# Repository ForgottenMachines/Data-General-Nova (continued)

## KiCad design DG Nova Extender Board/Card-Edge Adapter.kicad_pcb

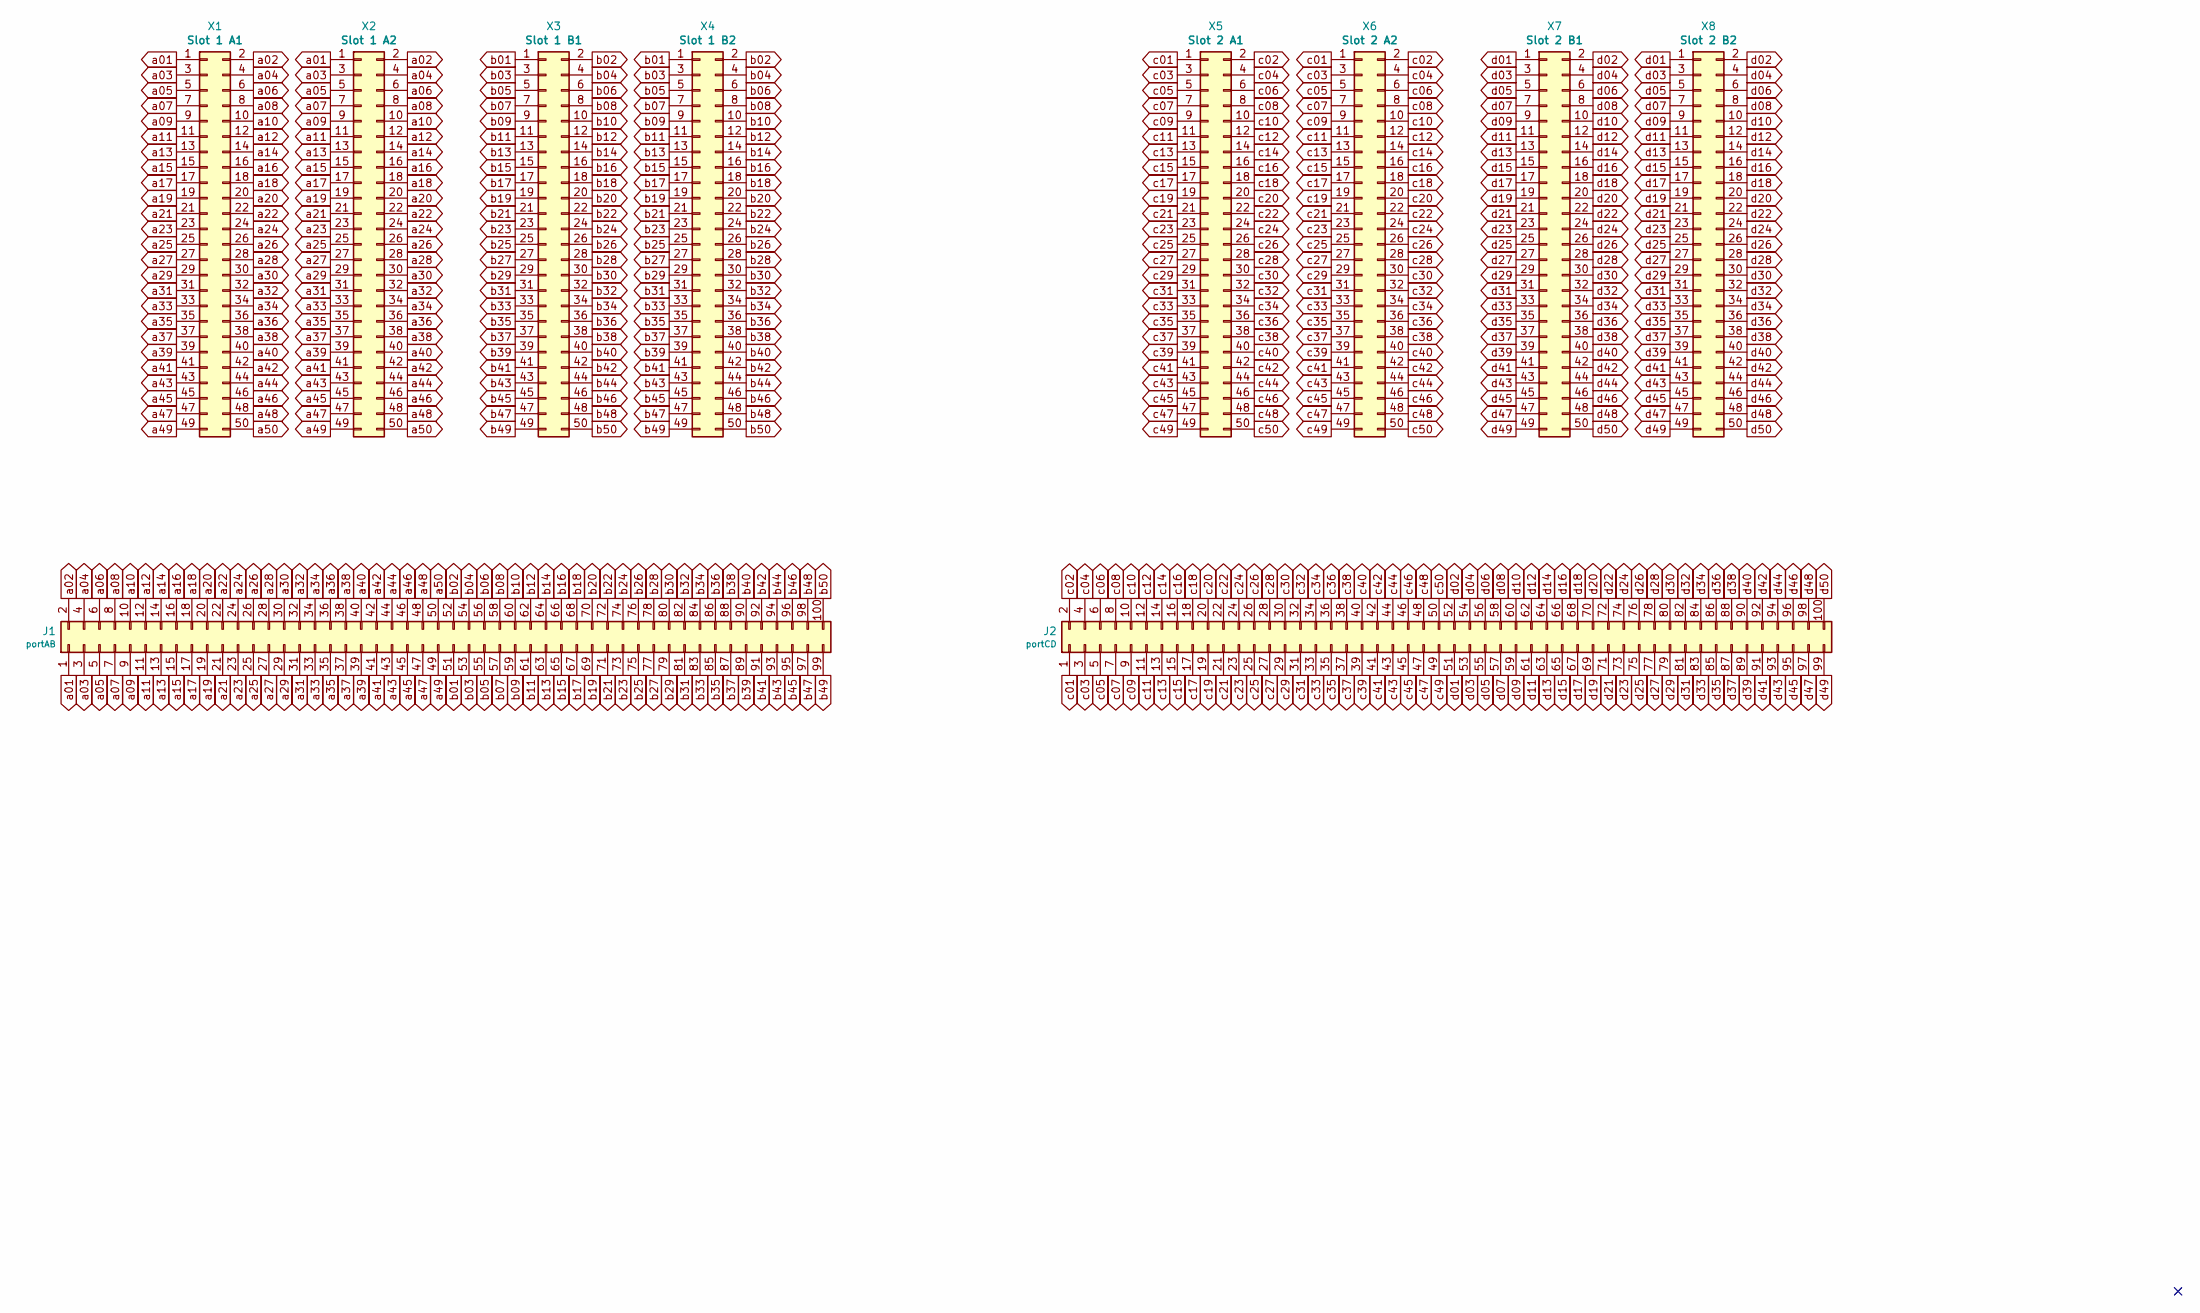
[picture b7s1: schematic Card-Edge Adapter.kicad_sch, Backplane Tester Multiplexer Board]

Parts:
J1: portAB; portA_NovaMod
J2: portCD; portB_NovaMod
X1: Slot 1 A1; IDC-Header_2x25_P2.54mm_Vertical; Part-Number SBH11-PBPC-D25-ST-BK; Digi-Key S9176-ND
X2: Slot 1 A2; IDC-Header_2x25_P2.54mm_Vertical; Part-Number SBH11-PBPC-D25-ST-BK; Digi-Key S9176-ND
X3: Slot 1 B1; IDC-Header_2x25_P2.54mm_Vertical; Part-Number SBH11-PBPC-D25-ST-BK; Digi-Key S9176-ND
X4: Slot 1 B2; IDC-Header_2x25_P2.54mm_Vertical; Part-Number SBH11-PBPC-D25-ST-BK; Digi-Key S9176-ND
X5: Slot 2 A1; IDC-Header_2x25_P2.54mm_Vertical; Part-Number SBH11-PBPC-D25-ST-BK; Digi-Key S9176-ND
X6: Slot 2 A2; IDC-Header_2x25_P2.54mm_Vertical; Part-Number SBH11-PBPC-D25-ST-BK; Digi-Key S9176-ND
X7: Slot 2 B1; IDC-Header_2x25_P2.54mm_Vertical; Part-Number SBH11-PBPC-D25-ST-BK; Digi-Key S9176-ND
X8: Slot 2 B2; IDC-Header_2x25_P2.54mm_Vertical; Part-Number SBH11-PBPC-D25-ST-BK; Digi-Key S9176-ND

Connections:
a01: J1.1, X1.1, X2.1
a02: J1.2, X1.2, X2.2
a03: J1.3, X1.3, X2.3
a04: J1.4, X1.4, X2.4
a05: J1.5, X1.5, X2.5
a06: J1.6, X1.6, X2.6
a07: J1.7, X1.7, X2.7
a08: J1.8, X1.8, X2.8
a09: J1.9, X1.9, X2.9
a10: J1.10, X1.10, X2.10
a11: J1.11, X1.11, X2.11
a12: J1.12, X1.12, X2.12
a13: J1.13, X1.13, X2.13
a14: J1.14, X1.14, X2.14
a15: J1.15, X1.15, X2.15
a16: J1.16, X1.16, X2.16
a17: J1.17, X1.17, X2.17
a18: J1.18, X1.18, X2.18
a19: J1.19, X1.19, X2.19
a20: J1.20, X1.20, X2.20
a21: J1.21, X1.21, X2.21
a22: J1.22, X1.22, X2.22
a23: J1.23, X1.23, X2.23
a24: J1.24, X1.24, X2.24
a25: J1.25, X1.25, X2.25
a26: J1.26, X1.26, X2.26
a27: J1.27, X1.27, X2.27
a28: J1.28, X1.28, X2.28
a29: J1.29, X1.29, X2.29
a30: J1.30, X1.30, X2.30
a31: J1.31, X1.31, X2.31
a32: J1.32, X1.32, X2.32
a33: J1.33, X1.33, X2.33
a34: J1.34, X1.34, X2.34
a35: J1.35, X1.35, X2.35
a36: J1.36, X1.36, X2.36
a37: J1.37, X1.37, X2.37
a38: J1.38, X1.38, X2.38
a39: J1.39, X1.39, X2.39
a40: J1.40, X1.40, X2.40
a41: J1.41, X1.41, X2.41
a42: J1.42, X1.42, X2.42
a43: J1.43, X1.43, X2.43
a44: J1.44, X1.44, X2.44
a45: J1.45, X1.45, X2.45
a46: J1.46, X1.46, X2.46
a47: J1.47, X1.47, X2.47
a48: J1.48, X1.48, X2.48
a49: J1.49, X1.49, X2.49
a50: J1.50, X1.50, X2.50
b01: J1.51, X3.1, X4.1
b02: J1.52, X3.2, X4.2
b03: J1.53, X3.3, X4.3
b04: J1.54, X3.4, X4.4
b05: J1.55, X3.5, X4.5
b06: J1.56, X3.6, X4.6
b07: J1.57, X3.7, X4.7
b08: J1.58, X3.8, X4.8
b09: J1.59, X3.9, X4.9
b10: J1.60, X3.10, X4.10
b11: J1.61, X3.11, X4.11
b12: J1.62, X3.12, X4.12
b13: J1.63, X3.13, X4.13
b14: J1.64, X3.14, X4.14
b15: J1.65, X3.15, X4.15
b16: J1.66, X3.16, X4.16
b17: J1.67, X3.17, X4.17
b18: J1.68, X3.18, X4.18
b19: J1.69, X3.19, X4.19
b20: J1.70, X3.20, X4.20
b21: J1.71, X3.21, X4.21
b22: J1.72, X3.22, X4.22
b23: J1.73, X3.23, X4.23
b24: J1.74, X3.24, X4.24
b25: J1.75, X3.25, X4.25
b26: J1.76, X3.26, X4.26
b27: J1.77, X3.27, X4.27
b28: J1.78, X3.28, X4.28
b29: J1.79, X3.29, X4.29
b30: J1.80, X3.30, X4.30
b31: J1.81, X3.31, X4.31
b32: J1.82, X3.32, X4.32
b33: J1.83, X3.33, X4.33
b34: J1.84, X3.34, X4.34
b35: J1.85, X3.35, X4.35
b36: J1.86, X3.36, X4.36
b37: J1.87, X3.37, X4.37
b38: J1.88, X3.38, X4.38
b39: J1.89, X3.39, X4.39
b40: J1.90, X3.40, X4.40
b41: J1.91, X3.41, X4.41
b42: J1.92, X3.42, X4.42
b43: J1.93, X3.43, X4.43
b44: J1.94, X3.44, X4.44
b45: J1.95, X3.45, X4.45
b46: J1.96, X3.46, X4.46
b47: J1.97 (Pin_69), X3.47, X4.47
b48: J1.98, X3.48, X4.48
b49: J1.99, X3.49, X4.49
b50: J1.100, X3.50, X4.50
c01: J2.1, X5.1, X6.1
c02: J2.2, X5.2, X6.2
c03: J2.3, X5.3, X6.3
c04: J2.4, X5.4, X6.4
c05: J2.5, X5.5, X6.5
c06: J2.6, X5.6, X6.6
c07: J2.7, X5.7, X6.7
c08: J2.8, X5.8, X6.8
c09: J2.9, X5.9, X6.9
c10: J2.10, X5.10, X6.10
c11: J2.11, X5.11, X6.11
c12: J2.12, X5.12, X6.12
c13: J2.13, X5.13, X6.13
c14: J2.14, X5.14, X6.14
c15: J2.15, X5.15, X6.15
c16: J2.16, X5.16, X6.16
c17: J2.17, X5.17, X6.17
c18: J2.18, X5.18, X6.18
c19: J2.19, X5.19, X6.19
c20: J2.20, X5.20, X6.20
c21: J2.21, X5.21, X6.21
c22: J2.22, X5.22, X6.22
c23: J2.23, X5.23, X6.23
c24: J2.24, X5.24, X6.24
c25: J2.25, X5.25, X6.25
c26: J2.26, X5.26, X6.26
c27: J2.27, X5.27, X6.27
c28: J2.28, X5.28, X6.28
c29: J2.29, X5.29, X6.29
c30: J2.30, X5.30, X6.30
c31: J2.31, X5.31, X6.31
c32: J2.32, X5.32, X6.32
c33: J2.33, X5.33, X6.33
c34: J2.34, X5.34, X6.34
c35: J2.35, X5.35, X6.35
c36: J2.36, X5.36, X6.36
c37: J2.37, X5.37, X6.37
c38: J2.38, X5.38, X6.38
c39: J2.39, X5.39, X6.39
c40: J2.40, X5.40, X6.40
c41: J2.41, X5.41, X6.41
c42: J2.42, X5.42, X6.42
c43: J2.43, X5.43, X6.43
c44: J2.44, X5.44, X6.44
c45: J2.45, X5.45, X6.45
c46: J2.46, X5.46, X6.46
c47: J2.47, X5.47, X6.47
c48: J2.48, X5.48, X6.48
c49: J2.49, X5.49, X6.49
c50: J2.50, X5.50, X6.50
d01: J2.51, X7.1, X8.1
d02: J2.52, X7.2, X8.2
d03: J2.53, X7.3, X8.3
d04: J2.54, X7.4, X8.4
d05: J2.55, X7.5, X8.5
d06: J2.56, X7.6, X8.6
d07: J2.57, X7.7, X8.7
d08: J2.58, X7.8, X8.8
d09: J2.59, X7.9, X8.9
d10: J2.60, X7.10, X8.10
d11: J2.61, X7.11, X8.11
d12: J2.62, X7.12, X8.12
d13: J2.63, X7.13, X8.13
d14: J2.64, X7.14, X8.14
d15: J2.65, X7.15, X8.15
d16: J2.66, X7.16, X8.16
d17: J2.67, X7.17, X8.17
d18: J2.68, X7.18, X8.18
d19: J2.69, X7.19, X8.19
d20: J2.70, X7.20, X8.20
d21: J2.71, X7.21, X8.21
d22: J2.72, X7.22, X8.22
d23: J2.73, X7.23, X8.23
d24: J2.74, X7.24, X8.24
d25: J2.75, X7.25, X8.25
d26: J2.76, X7.26, X8.26
d27: J2.77, X7.27, X8.27
d28: J2.78, X7.28, X8.28
d29: J2.79, X7.29, X8.29
d30: J2.80, X7.30, X8.30
d31: J2.81, X7.31, X8.31
d32: J2.82, X7.32, X8.32
d33: J2.83, X7.33, X8.33
d34: J2.84, X7.34, X8.34
d35: J2.85, X7.35, X8.35
d36: J2.86, X7.36, X8.36
d37: J2.87, X7.37, X8.37
d38: J2.88, X7.38, X8.38
d39: J2.89, X7.39, X8.39
d40: J2.90, X7.40, X8.40
d41: J2.91, X7.41, X8.41
d42: J2.92, X7.42, X8.42
d43: J2.93, X7.43, X8.43
d44: J2.94, X7.44, X8.44
d45: J2.95, X7.45, X8.45
d46: J2.96, X7.46, X8.46
d47: J2.97 (Pin_69), X7.47, X8.47
d48: J2.98, X7.48, X8.48
d49: J2.99, X7.49, X8.49
d50: J2.100, X7.50, X8.50

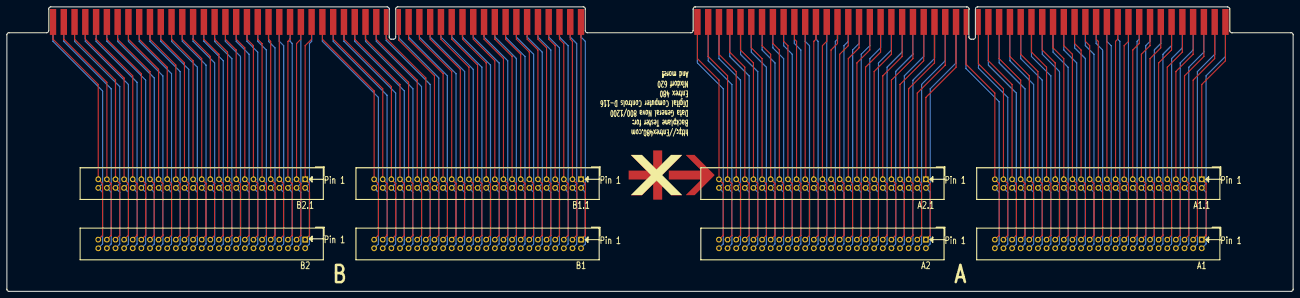
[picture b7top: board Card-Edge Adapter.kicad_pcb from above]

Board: 2 copper layers, 379.0 x 83.8 mm, 10 parts (0 on the bottom side), 200 nets.

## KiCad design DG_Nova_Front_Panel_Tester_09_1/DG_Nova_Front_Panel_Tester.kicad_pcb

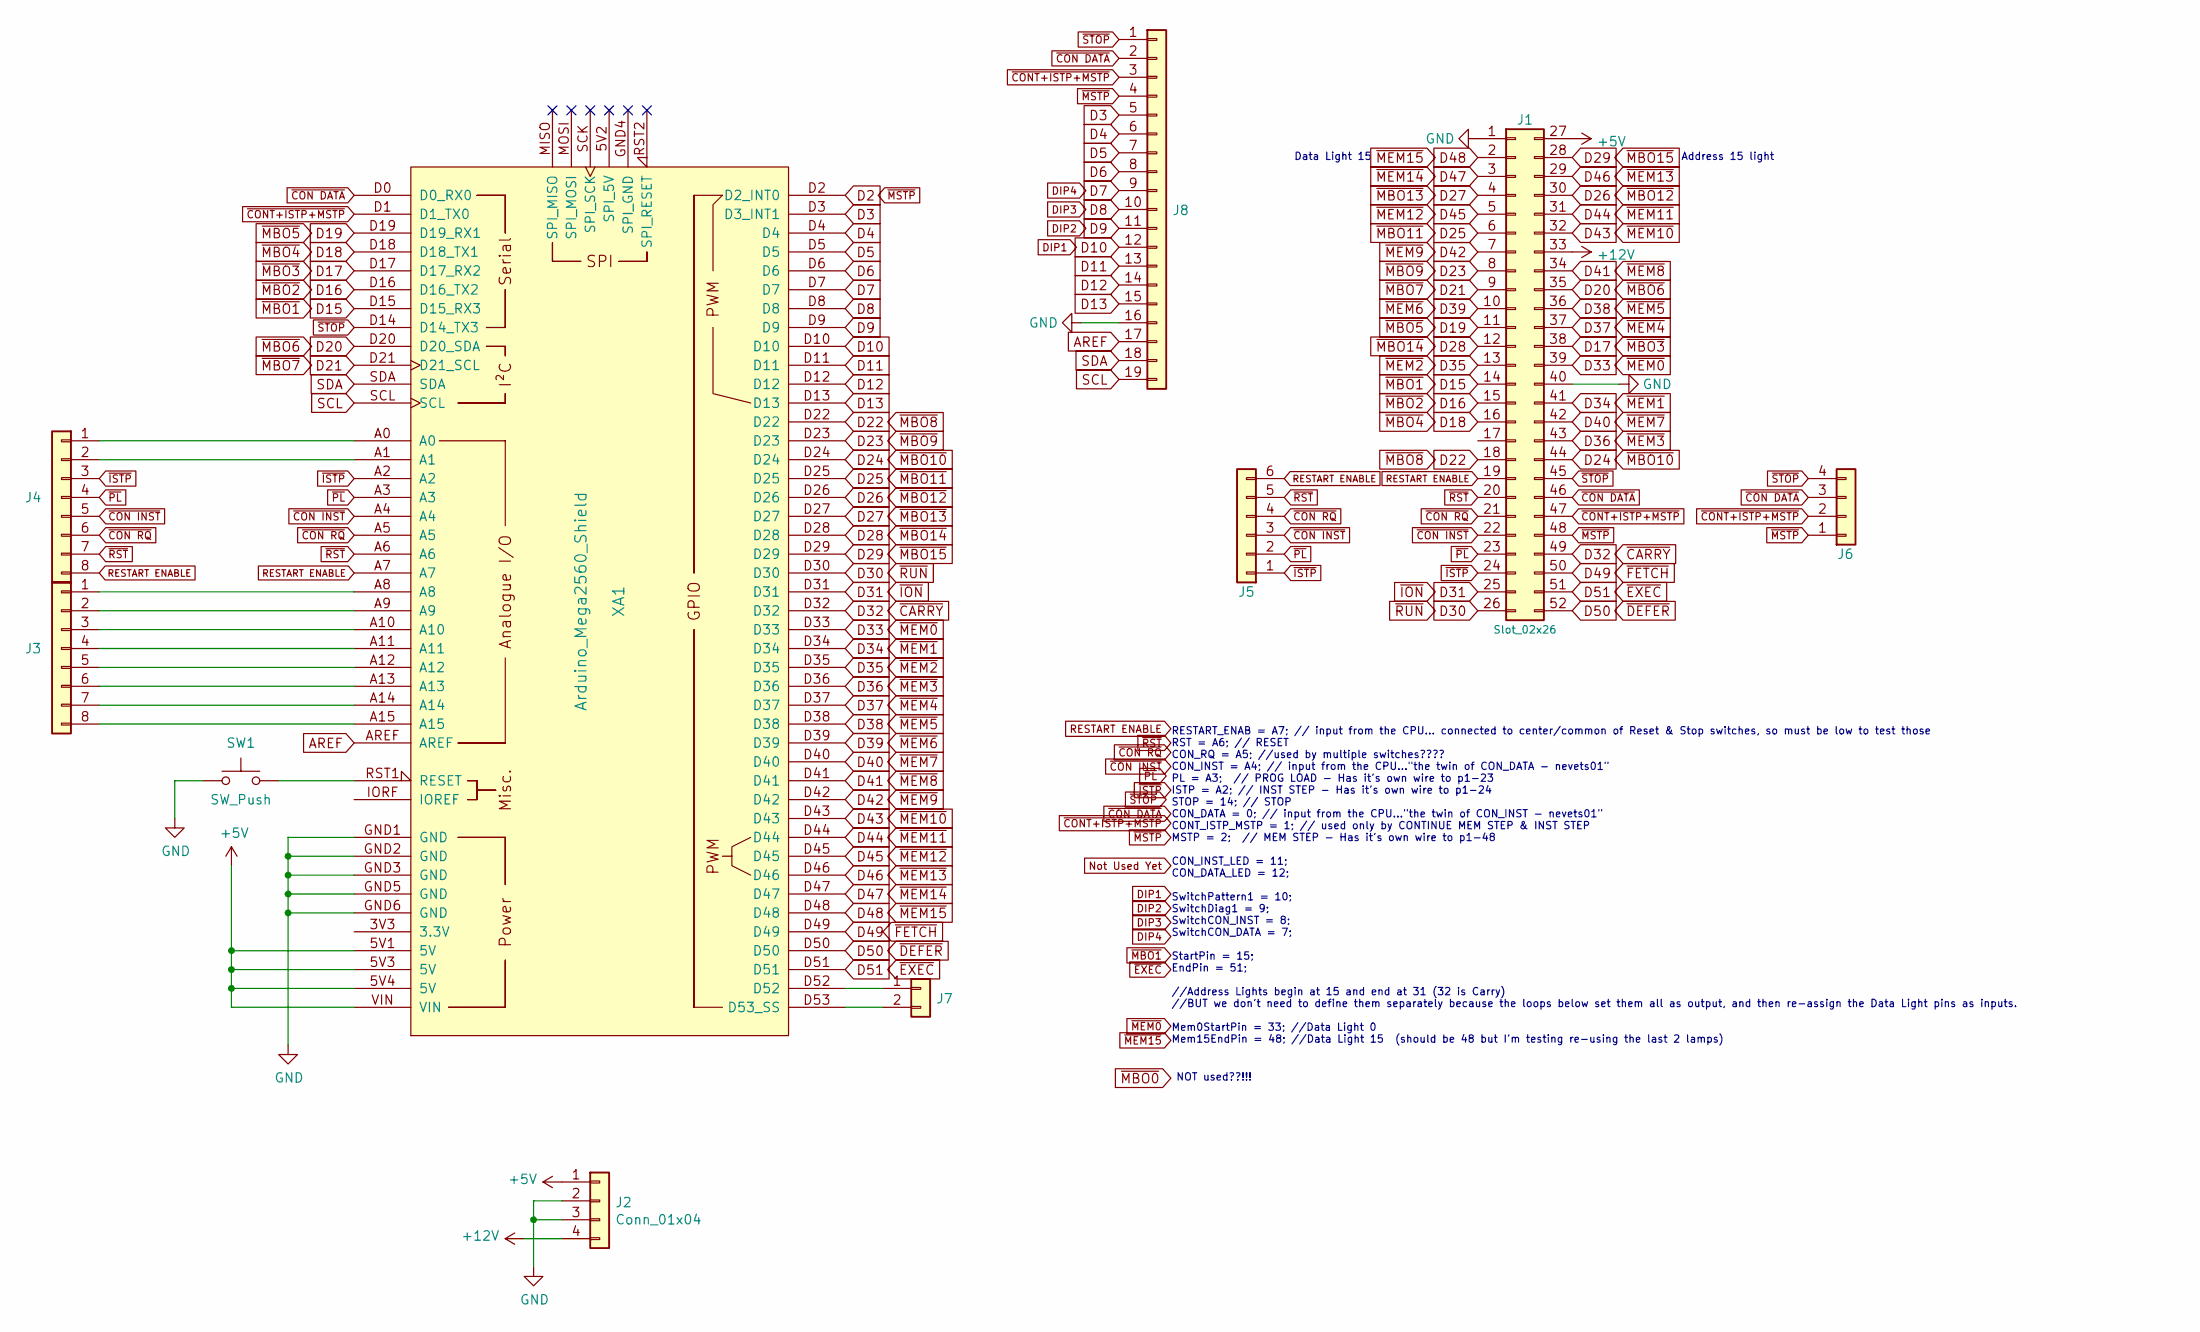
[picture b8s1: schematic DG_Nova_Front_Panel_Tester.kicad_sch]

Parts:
J1: Slot_02x26; port_Nova_52pin
J2, J6: Conn_01x04; PinHeader_1x04_P2.54mm_Vertical
J3, J4: Conn_01x08; PinHeader_1x08_P2.54mm_Vertical
J5: Conn_01x06; PinHeader_1x06_P2.54mm_Vertical
J7: Conn_01x02; PinHeader_1x02_P2.54mm_Vertical
J8: Conn_01x19; PinHeader_1x19_P2.54mm_Vertical
SW1: SW_Push; SW_PUSH_6mm
XA1: Arduino_Mega2560_Shield

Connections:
52: J7.2, XA1.D53 (D53_SS)
53: J7.1, XA1.D52
+5V: J1.27, J2.1, XA1.5V1 (5V), XA1.5V3 (5V), XA1.5V4 (5V), XA1.VIN
+12V: J1.33, J2.4
A0: J4.1, XA1.A0
A1: J4.2, XA1.A1
A8: J3.1, XA1.A8
A9: J3.2, XA1.A9
A10: J3.3, XA1.A10
A11: J3.4, XA1.A11
A12: J3.5, XA1.A12
A13: J3.6, XA1.A13
A14: J3.7, XA1.A14
A15: J3.8, XA1.A15
AREF: J8.17, XA1.AREF
D3: J8.5, XA1.D3 (D3_INT1)
D4: J8.6, XA1.D4
D5: J8.7, XA1.D5
D6: J8.8, XA1.D6
D7: J8.9, XA1.D7
D8: J8.10, XA1.D8
D9: J8.11, XA1.D9
D10: J8.12, XA1.D10
D11: J8.13, XA1.D11
D12: J8.14, XA1.D12
D13: J8.15, XA1.D13
D15: J1.14, XA1.D15 (D15_RX3)
D16: J1.15, XA1.D16 (D16_TX2)
D17: J1.38, XA1.D17 (D17_RX2)
D18: J1.16, XA1.D18 (D18_TX1)
D19: J1.11, XA1.D19 (D19_RX1)
D20: J1.35, XA1.D20 (D20_SDA)
D21: J1.9, XA1.D21 (D21_SCL)
D22: J1.18, XA1.D22
D23: J1.8, XA1.D23
D24: J1.44, XA1.D24
D25: J1.6, XA1.D25
D26: J1.30, XA1.D26
D27: J1.4, XA1.D27
D28: J1.12, XA1.D28
D29: J1.28, XA1.D29
D30: J1.26, XA1.D30
D31: J1.25, XA1.D31
D32: J1.49, XA1.D32
D33: J1.39, XA1.D33
D34: J1.41, XA1.D34
D35: J1.13, XA1.D35
D36: J1.43, XA1.D36
D37: J1.37, XA1.D37
D38: J1.36, XA1.D38
D39: J1.10, XA1.D39
D40: J1.42, XA1.D40
D41: J1.34, XA1.D41
D42: J1.7, XA1.D42
D43: J1.32, XA1.D43
D44: J1.31, XA1.D44
D45: J1.5, XA1.D45
D46: J1.29, XA1.D46
D47: J1.3, XA1.D47
D48: J1.2, XA1.D48
D49: J1.50, XA1.D49
D50: J1.52, XA1.D50
D51: J1.51, XA1.D51
GND: J1.1, J1.40, J2.2, J2.3, J8.16, SW1.1, XA1.GND1 (GND), XA1.GND2 (GND), XA1.GND3 (GND), XA1.GND5 (GND), XA1.GND6 (GND); also elsewhere on the board
unnamed 65: SW1.2, XA1.RST1 (RESET); also elsewhere on the board
RESTART ENABLE: J1.19, J4.8, J5.6, XA1.A7
SCL: J8.19, XA1.SCL
SDA: J8.18, XA1.SDA
~CON DATA: J1.46, J6.3, J8.2, XA1.D0 (D0_RX0)
~CON INST: J1.22, J4.5, J5.3, XA1.A4
~CON RQ: J1.21, J4.6, J5.4, XA1.A5
~CONT+ISTP+MSTP: J1.47, J6.2, J8.3, XA1.D1 (D1_TX0)
~ISTP: J1.24, J4.3, J5.1, XA1.A2
~PL: J1.23, J4.4, J5.2, XA1.A3
~RST: J1.20, J4.7, J5.5, XA1.A6
~STOP: J1.45, J6.4, J8.1, XA1.D14 (D14_TX3)

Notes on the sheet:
Address 15 light
RESTART_ENAB = A7; // input from the CPU... connected to center/common of Reset & Stop switches, so must be low to test those RST = A6; // RESET CON_RQ = A5; //used by multiple switches???? CON_INST = A4; // input from the CPU..."the twin of CON_DATA - nevets01" PL = A3; // PROG LOAD - Has it's own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
Data Light 15
NOT used??!!!

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
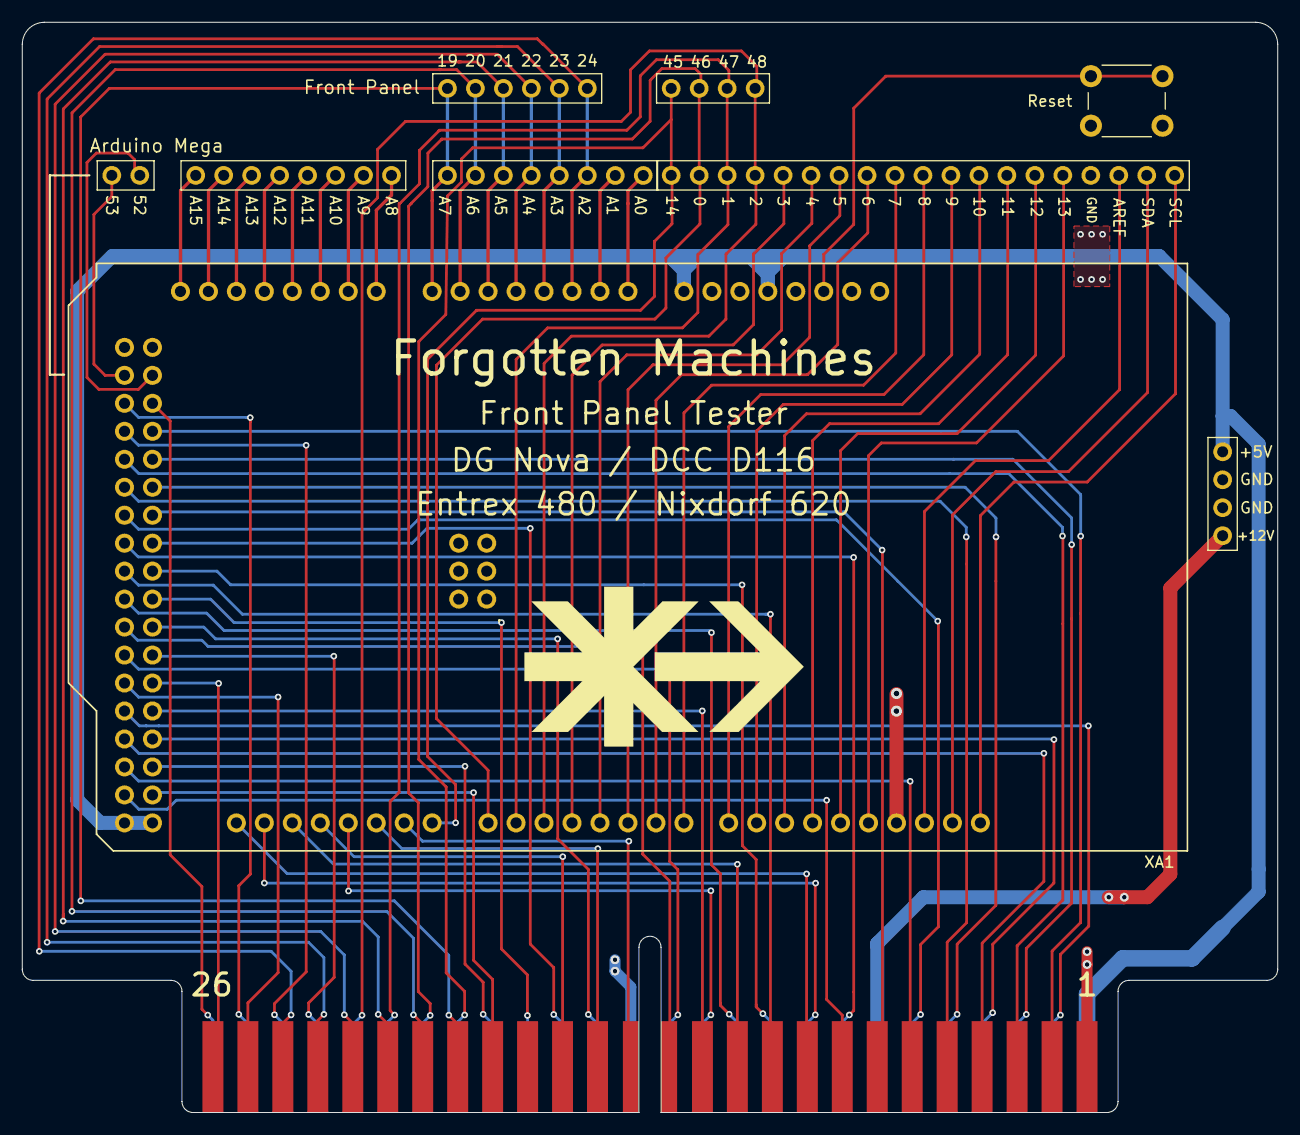
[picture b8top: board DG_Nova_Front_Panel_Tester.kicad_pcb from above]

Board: 2 copper layers, 114.0 x 99.0 mm, 10 parts (0 on the bottom side), 77 nets.

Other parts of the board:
Reset: SW_Push; SW_PUSH_6mm

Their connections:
GND: Reset.1; also elsewhere on the board
unnamed 65: Reset.2; also elsewhere on the board

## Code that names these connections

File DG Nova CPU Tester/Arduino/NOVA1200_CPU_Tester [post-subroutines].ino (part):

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String Upper = "";
String Lower = "";

constexpr int DataPin1 = 3;  
constexpr int ClockPin1 = 4; 
constexpr int LatchPin1 = 5; 
constexpr int DataPin2 = 6;  
constexpr int ClockPin2 = 11; 
constexpr int LatchPin2 = 12; 

constexpr int RESTART_ENAB = A7; // input from the CPU... connected to center/common of Reset & Stop switches, so must be low to test those
constexpr int RST = A6; // RESET
constexpr int CON_RQ = A5; //used by multiple switches????
constexpr int CON_INST = A4; // input from the CPU..."the twin of CON_DATA - nevets01"
constexpr int PL = A3;  // PROG LOAD - Has it's own wire to p1-23 
constexpr int ISTP = A2; // INST STEP - Has it's own wire to p1-24
constexpr int STOP = 14; // STOP
constexpr int CON_DATA = 0; // input from the CPU..."the twin of CON_INST - nevets01"
constexpr int CONT_ISTP_MSTP = 1; // used only by CONTINUE MEM STEP & INST STEP
constexpr int MSTP = 2;  // MEM STEP - Has it's own wire to p1-48

constexpr int CON_INST_LED = 11;  
constexpr int CON_DATA_LED = 12; 
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constexpr int SwitchCON_INST = 8;
constexpr int SwitchCON_DATA = 7;

constexpr int MEM0 = A15;
constexpr int MEM1 = A14;
constexpr int MEM2 = A13;
constexpr int MEM3 = A12;
constexpr int MEM4 = A11;
constexpr int MEM5 = A10;
constexpr int MEM6 = A9;
constexpr int MEM7 = A8;

constexpr int StartPin = 15;
constexpr int EndPin = 51;
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constexpr int blinky = 10;
constexpr int fastcycle = 0;

constexpr int DIP1 = 7;
constexpr int DIP2 = 8;
constexpr int DIP3 = 9;
constexpr int DIP4 = 10;


void setup() {
//       Serial.begin(115200);  //Using this MAY hijack pins D0-D1, which is hard-wired to /CON DATA & /CONT+ISTP+MSTP.
//       Serial.println("====================");
       pinMode(SwitchPattern1, INPUT_PULLUP);
       pinMode(SwitchDiag1, INPUT_PULLUP);
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       digitalWrite(CON_RQ, HIGH); 
       pinMode(CON_INST, INPUT_PULLUP);
       pinMode(PL, INPUT_PULLUP);
       pinMode(ISTP, INPUT_PULLUP);
       pinMode(STOP, OUTPUT);
       digitalWrite(STOP, HIGH);
       pinMode(CON_DATA, INPUT_PULLUP);
       pinMode(CONT_ISTP_MSTP, INPUT_PULLUP);
       pinMode(MSTP, INPUT_PULLUP);

       pinMode(RESTART_ENAB, INPUT);
       pinMode(CON_INST, INPUT_PULLUP);
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       pinMode(CON_INST_LED, OUTPUT);  
       pinMode(CON_DATA_LED, OUTPUT); 

       pinMode(MEM0, OUTPUT); 
       pinMode(MEM1, OUTPUT); 
       pinMode(MEM2, OUTPUT); 
       pinMode(MEM3, OUTPUT); 
       pinMode(MEM4, OUTPUT); 
       pinMode(MEM5, OUTPUT); 
       pinMode(MEM6, OUTPUT); 
       pinMode(MEM7, OUTPUT); 
     


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  
// set mode switches on tester board

  pinMode(DIP1, INPUT_PULLUP);
  pinMode(DIP2, INPUT_PULLUP);
  pinMode(DIP3, INPUT_PULLUP);
  pinMode(DIP4, INPUT_PULLUP);

  digitalWrite(MEM0, HIGH);
  digitalWrite(MEM1, HIGH);
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//Serial.println("");


  pinMode(DataPin1, OUTPUT); 
  pinMode(ClockPin1, OUTPUT);  
  pinMode(LatchPin1, OUTPUT);
  pinMode(DataPin2, OUTPUT);  
  pinMode(ClockPin2, OUTPUT);  
  pinMode(LatchPin2, OUTPUT);

}

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pinMode(CON_INST, INPUT_PULLUP);
pinMode(CON_DATA, INPUT_PULLUP);
pinMode(CONT_ISTP_MSTP, INPUT_PULLUP);
pinMode(MSTP, INPUT_PULLUP);
pinMode(ISTP, INPUT_PULLUP);
pinMode(PL, INPUT_PULLUP);
pinMode(RESTART_ENAB, INPUT);
  for (int i = StartPin; i <= EndPin; i = i + 1) {   //For Testing all the pretty lights
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delay(DelayAmount);  

///////SET ADDRESSES HERE
digitalWrite(LatchPin1,LOW);  //Send bits 0-7 into the 74
for (uint8_t i = Upper.length(); i >0 ; i--)  {
  digitalWrite(DataPin1, Upper.charAt(i-1)&0x01);               
  digitalWrite(ClockPin1, HIGH);
  digitalWrite(ClockPin1, LOW);   
}
digitalWrite(LatchPin1,HIGH);
digitalWrite(LatchPin2,LOW);  //Send bits 8-15 into the other 74
for (uint8_t j = Lower.length(); j >0 ; j--)  {
  digitalWrite(DataPin2, Lower.charAt(j-1)&0x01);               
  digitalWrite(ClockPin2, HIGH);
  digitalWrite(ClockPin2, LOW);   
}
digitalWrite(LatchPin2,HIGH);
///END SET ADDRESSES

digitalWrite(MEM0, HIGH);  ///front panel code for EXAMINE (NOTE: these signals are inverted from how the NOVA sees them)
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pinMode(CON_INST, OUTPUT);
pinMode(CON_DATA, OUTPUT);
pinMode(CONT_ISTP_MSTP, OUTPUT);
pinMode(MSTP, OUTPUT);
pinMode(ISTP, OUTPUT);
pinMode(PL, OUTPUT);
pinMode(RST, OUTPUT);
pinMode(RESTART_ENAB, OUTPUT);
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
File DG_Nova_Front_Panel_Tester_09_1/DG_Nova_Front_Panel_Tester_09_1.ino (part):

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constexpr int CON_RQ = A5; //used by multiple switches????
constexpr int CON_INST = A4; // input from the CPU..."the twin of CON_DATA - nevets01"
constexpr int PL = A3;  // PROG LOAD - Has it's own wire to p1-23 
constexpr int ISTP = A2; // INST STEP - Has it's own wire to p1-24
constexpr int STOP = 14; // STOP
constexpr int CON_DATA = 0; // input from the CPU..."the twin of CON_INST - nevets01"
constexpr int CONT_ISTP_MSTP = 1; // used only by CONTINUE MEM STEP & INST STEP
constexpr int MSTP = 2;  // MEM STEP - Has it's own wire to p1-48

constexpr int CON_INST_LED = 11;  
constexpr int CON_DATA_LED = 12; 
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constexpr int fastcycle = 0;

//for the single legacy board DIP switch arrangement
//constexpr int DIP1 = 10;
//constexpr int DIP2 = 9;
//constexpr int DIP3 = 8;
//constexpr int DIP4 = 7;

//for upgraded boards only DIP switch arrangement
constexpr int DIP1 = 7;
constexpr int DIP2 = 8;
constexpr int DIP3 = 9;
constexpr int DIP4 = 10;

void setup() {
       pinMode(SwitchPattern1, INPUT_PULLUP);
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       pinMode(CON_RQ, INPUT_PULLUP);
       pinMode(CON_INST, INPUT_PULLUP);
       pinMode(PL, INPUT_PULLUP);
       pinMode(ISTP, INPUT_PULLUP);
       pinMode(STOP, INPUT_PULLUP);
       pinMode(CON_DATA, INPUT_PULLUP);
       pinMode(CONT_ISTP_MSTP, INPUT_PULLUP);
       pinMode(MSTP, INPUT_PULLUP);

       pinMode(RESTART_ENAB, OUTPUT);
       pinMode(CON_INST, OUTPUT);  
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
// set mode switches on tester board

  pinMode(DIP1, INPUT_PULLUP);
  pinMode(DIP2, INPUT_PULLUP);
  pinMode(DIP3, INPUT_PULLUP);
  pinMode(DIP4, INPUT_PULLUP);

//  Serial.begin(115200);  //Enabling Serial hijacks/breaks D0 and D1, and thus hijacks CON_DATA & CONT_ISTP_MSTP
  Serial.println("Arduino Live!");
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pinMode(CON_INST, INPUT_PULLUP);
pinMode(CON_DATA, INPUT_PULLUP);
pinMode(CONT_ISTP_MSTP, INPUT_PULLUP);
pinMode(MSTP, INPUT_PULLUP);
pinMode(ISTP, INPUT_PULLUP);
pinMode(PL, INPUT_PULLUP);
pinMode(RST, INPUT_PULLUP);

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///////////////////////////////////////////////////////////////////////////////////////////////////////////////////////////

//turn off all of the Address lights that might have been left on from the previous operation
for (int i = Mem0StartPin + 1; i <= Mem15EndPin; i = i + 1) {  //loop through all data switch signals except for 0 (becauze we use Carry for that)
digitalWrite(i-19, HIGH); //turn off all of the address lights
}
digitalWrite(32, HIGH); //turn off the Carry light
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    digitalWrite(31, HIGH); 
    }

//make con_RQ to RUN cuz most switches signal this pin?

 if (digitalRead(CON_RQ) == LOW){ // ????
    digitalWrite(30, LOW); //RUN light
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pinMode(CON_INST, OUTPUT);
pinMode(CON_DATA, OUTPUT);
pinMode(CONT_ISTP_MSTP, OUTPUT);
pinMode(MSTP, OUTPUT);
pinMode(ISTP, OUTPUT);
pinMode(PL, OUTPUT);
pinMode(RST, OUTPUT);

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
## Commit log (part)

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2023-05-18 PSU board
2023-12-02 build
2023-12-02 Rename
2023-12-03 Create IC Chips in Spreadsheet
2023-12-03 Update IC Chips in Spreadsheet
2023-12-06 Images
2023-12-06 photos
2023-12-08 Deep Dives
2023-12-12 Add Sync
2023-12-12 front panel tester
2023-12-13 Rename Nova Signals Definitions.pdf to Nova 1200 Signals Definitions.pdf
2023-12-13 Cleanup
2024-01-09 tester
2024-01-11 makinmg
2024-01-11 El Classico
2024-01-11 more
2024-01-13 junk
2024-01-14 crazy
2024-01-14 More Magic
2024-01-14 card extender
2024-01-15 stuff
2024-01-15 swap connectors
2024-01-15 yeah
2024-01-26 mega-magic
2024-01-27 docs
2024-01-27 tweak
2024-01-28 work
2024-01-28 nothing
2024-01-28 arrange
2024-01-28 board
2024-01-28 footprint
2024-01-28 Add Quantx
2024-01-28 Update fp-info-cache
2024-01-30 big build
2024-01-30 TRACE
2024-02-02 Marcel
2024-02-02 All Traces Removed
2024-02-02 All Board Signal Traces Pulled Up
2024-02-03 All Top Signal Traces Pulled Down
2024-02-03 Progress!
2024-02-03 ALL Backplane Sockets Connected
2024-02-03 All Front Panel Control Signals
2024-02-03 All Front Panel Control Signals 2
2024-02-03 Arduino Placement
2024-02-03 Intense
2024-02-03 Arduino connected to signals but not Front Panel Connector or status lights/pinouts
2024-02-03 All the Control Panel Lights, but still not the Front Panel Connectors
2024-02-04 Before KiCad 7.0.10 Upgrade
2024-02-04 Front Panel Connectors FINALLY connected
2024-02-04 Right before PSU signal control insertion
2024-02-04 Done right BEFORE Ground & 5v Fill
2024-02-04 All DONE except for LOGOS
2024-02-04 FM Logo
2024-02-05 Did I get lost?
2024-02-05 After Logo Montage
2024-02-07 3D LED Bar
2024-02-07 3D LED .WRL file
2024-02-07 Piggyback 3v3
2024-02-08 Add Reset Button & Shottky Diode to Pico
2024-02-08 Some DRC Cleanup, add 3v3 to back board
2024-02-08 Jumpers & Shottkys
2024-02-08 3v3 to 5v work
2024-02-08 GPIO research
2024-02-09 3D models LED bars smaller sizes fixed
2024-02-09 URLs
2024-02-09 misc
2024-02-28 QuantX schematic update
2024-03-16 Nova 2 CPU
2024-03-16 DG Nova Manuals
2024-04-19 open source
2024-04-20 atx update
2024-04-21 power switch
2024-04-21 atx fix
2024-04-21 repairs
2024-04-21 archive DRC version with ground break
2024-04-22 whoops
2024-04-22 Power-Up Timing
2024-04-27 4.7uf polarized
2024-04-29 Huzifa fixes grounds
2024-07-25 mirror signals for reference
2024-07-26 front panel diagram
2024-07-30 PDF of Backplane Sch
2024-07-31 test
2024-07-31 TESTS
2024-07-31 isolation
2024-08-01 Expand
2024-08-03 yikes
2024-08-05 datasheets
2024-08-05 adjust
2024-08-13 Examine by Arduino
2024-08-21 74LS32
2024-09-07 vcfmw
2024-12-27 MAJOR CHANGES
2024-12-28 Advance the test
2025-01-02 neaten
2025-02-01 more mem
2025-02-11 Done?
2025-02-11 gerbers
2025-02-23 fix /CE to GND
2025-03-12 Fix reset button polarity
2025-03-12 UPGRADE
2025-03-13 upgrades
2025-03-14 arduino
2025-03-15 housekeep
2025-03-16 Address Control
2025-03-16 progress
2025-03-16 building
2025-03-17 74179 replacement
2025-03-25 revisions
2025-03-29 True
2025-03-29 test6
2025-05-18 Lots o updates
2025-05-22 Testing with JoeZ
2025-05-22 Wow, fixed the FeRAM - It's the NOVA CPU Tester!
2025-05-23 KiCad 9 and LED Buffers!
2025-06-12 Marty
2025-09-25 4077 by Nevets
2026-05-13 update schematic to work with KiCad correctly
2026-05-13 update schematic pdf + profile files
